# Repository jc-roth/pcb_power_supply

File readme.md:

# pcb_power_supply
This repository contains the KiCAD schematic/PCB files for a linear and switching power supply board that can be used to power boards using the template in [this repo](https://github.com/jc-roth/pcb_kicad_template).

## Building/operating the circuit
Either directly download gerber and BOM files from the releases page or download the KiCAD project and export to your liking. Feel free to shoot me an email with any questions.

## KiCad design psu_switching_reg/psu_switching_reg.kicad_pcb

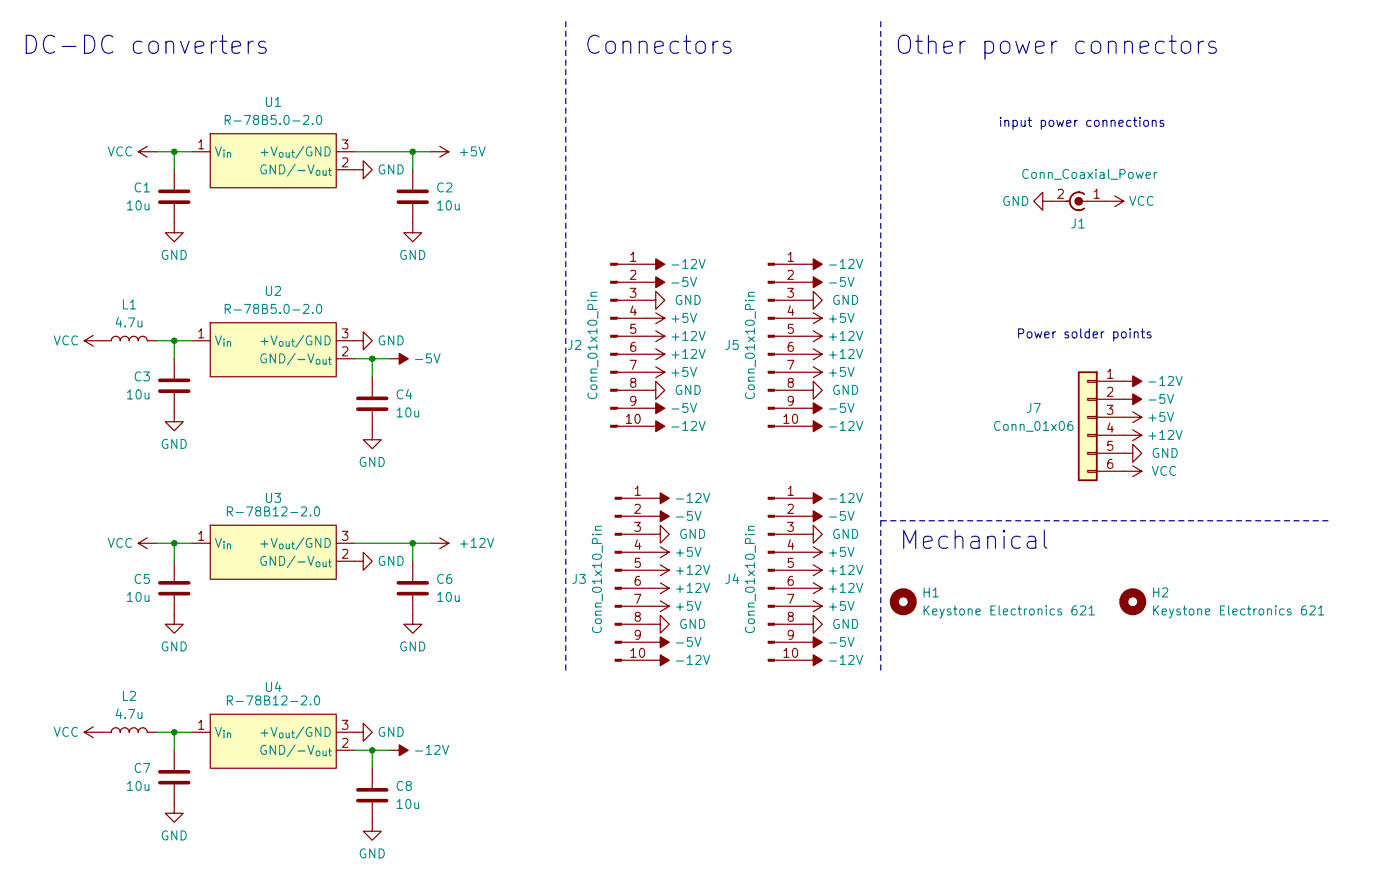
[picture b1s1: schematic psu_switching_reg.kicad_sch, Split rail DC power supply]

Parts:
C1, C2, C3, C4, C5, C6, C7, C8: 10u; C_0805_2012Metric_Pad1.18x1.45mm_HandSolder; JLCPCB PN C440198
H1, H2: Keystone Electronics 621; Keystone 621; Digikey PN 36-621-ND
J1: Conn_Coaxial_Power; CUI_PJ-037B; Digikey PN CP-037B-ND
J2, J3, J4, J5: Conn_01x10_Pin; JST_ZH_B10B-ZR_1x10_P1.50mm_Vertical; Digikey PN 455-S10B-ZR-ND
J7: Conn_01x06; SolderWire-1sqmm_1x06_P5.4mm_D1.4mm_OD2.7mm
L1, L2: 4.7u; L_Axial_L7.0mm_D3.3mm_P2.54mm_Vertical_Fastron_MICC; Digikey PN 535-AIAP-01-4R7K-TCT-ND
U1, U2: R-78B5.0-2.0; R-78Bxx-2.0; Digikey PN 945-3042-ND
U3, U4: R-78B12-2.0; R-78Bxx-2.0; Digikey PN 945-3041-ND

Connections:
+5V: C2.1, J2.4, J2.7, J3.4, J3.7, J4.4, J4.7, J5.4, J5.7, J7.3, U1.3 (+V_{out}/GND)
+12V: C6.1, J2.5, J2.6, J3.5, J3.6, J4.5, J4.6, J5.5, J5.6, J7.4, U3.3 (+V_{out}/GND)
-5V: C4.1, J2.2, J2.9, J3.2, J3.9, J4.2, J4.9, J5.2, J5.9, J7.2, U2.2 (GND/-V_{out})
-12V: C8.1, J2.1, J2.10, J3.1, J3.10, J4.1, J4.10, J5.1, J5.10, J7.1, U4.2 (GND/-V_{out})
GND: C1.2, C2.2, C3.2, C4.2, C5.2, C6.2, C7.2, C8.2, J1.2 (Ext), J2.3, J2.8, J3.3, J3.8, J4.3, J4.8, J5.3, J5.8, J7.5, U1.2 (GND/-V_{out}), U2.3 (+V_{out}/GND), U3.2 (GND/-V_{out}), U4.3 (+V_{out}/GND)
unnamed: C3.1, L1.2, U2.1 (V_{in})
unnamed: C7.1, L2.2, U4.1 (V_{in})
VCC: C1.1, C5.1, J1.1 (In), J7.6, L1.1, L2.1, U1.1 (V_{in}), U3.1 (V_{in})

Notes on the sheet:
Other power connectors
Power solder points
input power connections
Mechanical
DC-DC converters
Connectors

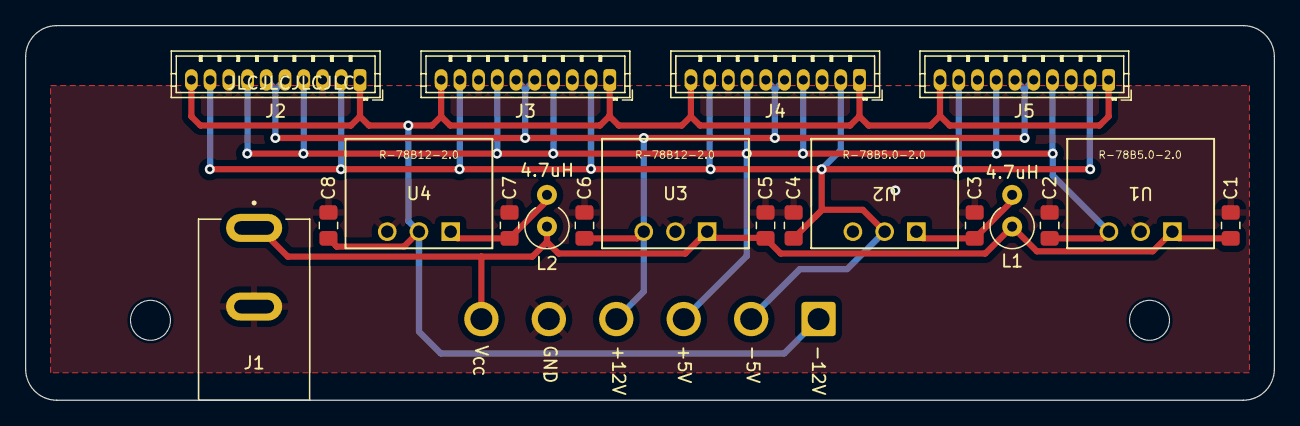
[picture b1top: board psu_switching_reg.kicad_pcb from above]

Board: 2 copper layers, 100.0 x 30.0 mm, 22 parts (0 on the bottom side), 8 nets.

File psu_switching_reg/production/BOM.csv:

"Reference","Value","Datasheet","Footprint","Qty","DNP","Digikey PN","JLCPCB PN"
"C1,C2,C3,C4,C5,C6,C7,C8","10u","~","Capacitor_SMD:C_0805_2012Metric_Pad1.18x1.45mm_HandSolder","8","","","C440198"
"H1,H2","Keystone Electronics 621","~","matterwaves:Keystone 621","2","","36-621-ND",""
"J1","Conn_Coaxial_Power","~","matterwaves:CUI_PJ-037B","1","","CP-037B-ND",""
"J2,J3,J4,J5","Conn_01x10_Pin","~","Connector_JST:JST_ZH_B10B-ZR_1x10_P1.50mm_Vertical","4","","455-S10B-ZR-ND",""
"L1,L2","4.7u","~","Inductor_THT:L_Axial_L7.0mm_D3.3mm_P2.54mm_Vertical_Fastron_MICC","2","","535-AIAP-01-4R7K-TCT-ND",""
"U1,U2","R-78B5.0-2.0","https://g.recomcdn.com/media/Datasheet/pdf/.fldP_2rX/.t124a6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","matterwaves:R-78Bxx-2.0","2","","945-3042-ND",""
"U3,U4","R-78B12-2.0","https://g.recomcdn.com/media/Datasheet/pdf/.fldP_2rX/.t124a6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","matterwaves:R-78Bxx-2.0","2","","945-3041-ND",""

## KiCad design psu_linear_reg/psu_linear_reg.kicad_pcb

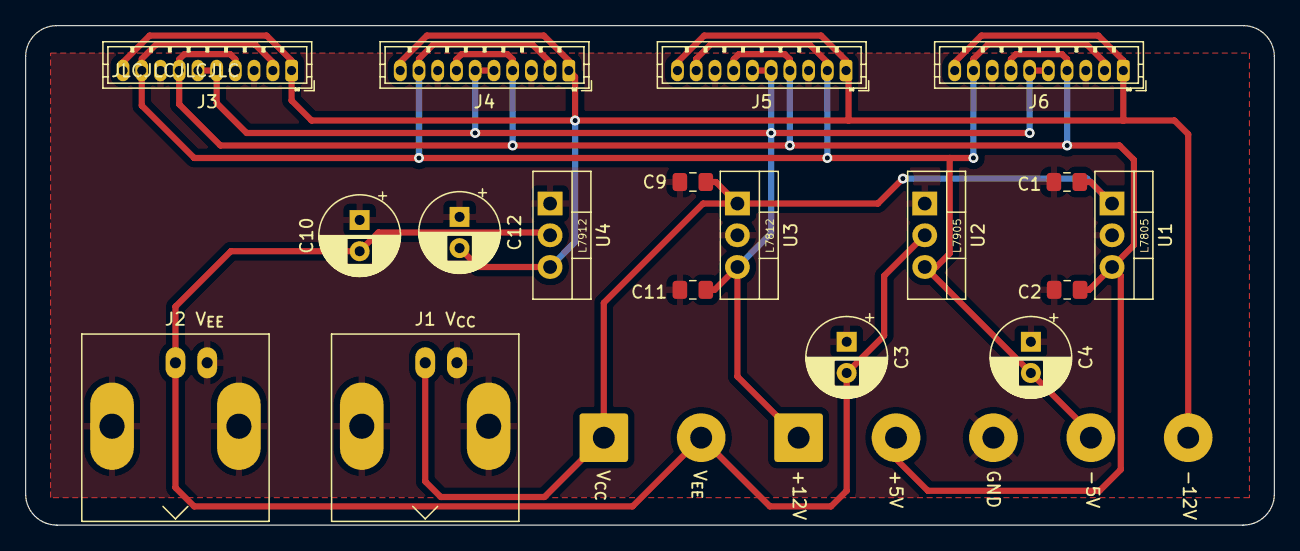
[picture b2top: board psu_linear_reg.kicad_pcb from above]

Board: 2 copper layers, 100.0 x 40.0 mm, 20 parts (0 on the bottom side), 7 nets.

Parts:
C1, C9: 330n; C_0805_2012Metric_Pad1.18x1.45mm_HandSolder
C2, C11: 100n; C_0805_2012Metric_Pad1.18x1.45mm_HandSolder
C3, C10: 2.2u; CP_Radial_D6.3mm_P2.50mm
C4, C12: 1u; CP_Radial_D6.3mm_P2.50mm
J1, J2: Conn_Coaxial_Power; BNC_Molex_0731385033
J3, J4, J5, J6: Conn_01x10_Pin; JST_ZH_B10B-ZR_1x10_P1.50mm_Vertical
J7: Conn_01x05; SolderWire-1sqmm_1x05_P7.8mm_D1.4mm_OD3.9mm
J8: Conn_01x02; SolderWire-1sqmm_1x02_P7.8mm_D1.4mm_OD3.9mm
U1: L7805; TO-220-3_Vertical
U2: L7905; TO-220-3_Vertical
U3: L7812; TO-220-3_Vertical
U4: L7912; TO-220-3_Vertical

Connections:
+5V: C2.1, J3.4, J3.7, J4.4, J4.7, J5.4, J5.7, J6.4, J6.7, J7.2, U1.3 (OUT)
+12V: C11.1, J3.5, J3.6, J4.5, J4.6, J5.5, J5.6, J6.5, J6.6, J7.1, U3.3 (OUT)
-5V: C4.2, J3.2, J3.9, J4.2, J4.9, J5.2, J5.9, J6.2, J6.9, J7.4, U2.3 (VO)
-12V: C12.2, J3.1, J3.10, J4.1, J4.10, J5.1, J5.10, J6.1, J6.10, J7.5, U4.3 (VO)
GND: C1.2, C2.2, C3.1, C4.1, C9.2, C10.1, C11.2, C12.1, J1.2 (Ext), J2.2 (Ext), J3.3, J3.8, J4.3, J4.8, J5.3, J5.8, J6.3, J6.8, J7.3, U1.2 (GND), U2.1 (GND), U3.2 (GND), U4.1 (GND)
VCC: C1.1, C9.1, J1.1 (In), J8.1, U1.1 (IN), U3.1 (IN)
VEE: C3.2, C10.2, J2.1 (In), J8.2, U2.2 (VI), U4.2 (VI)

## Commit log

2025-09-30 Updated .gitignore
2025-09-30 Added linear and switching PSUs
